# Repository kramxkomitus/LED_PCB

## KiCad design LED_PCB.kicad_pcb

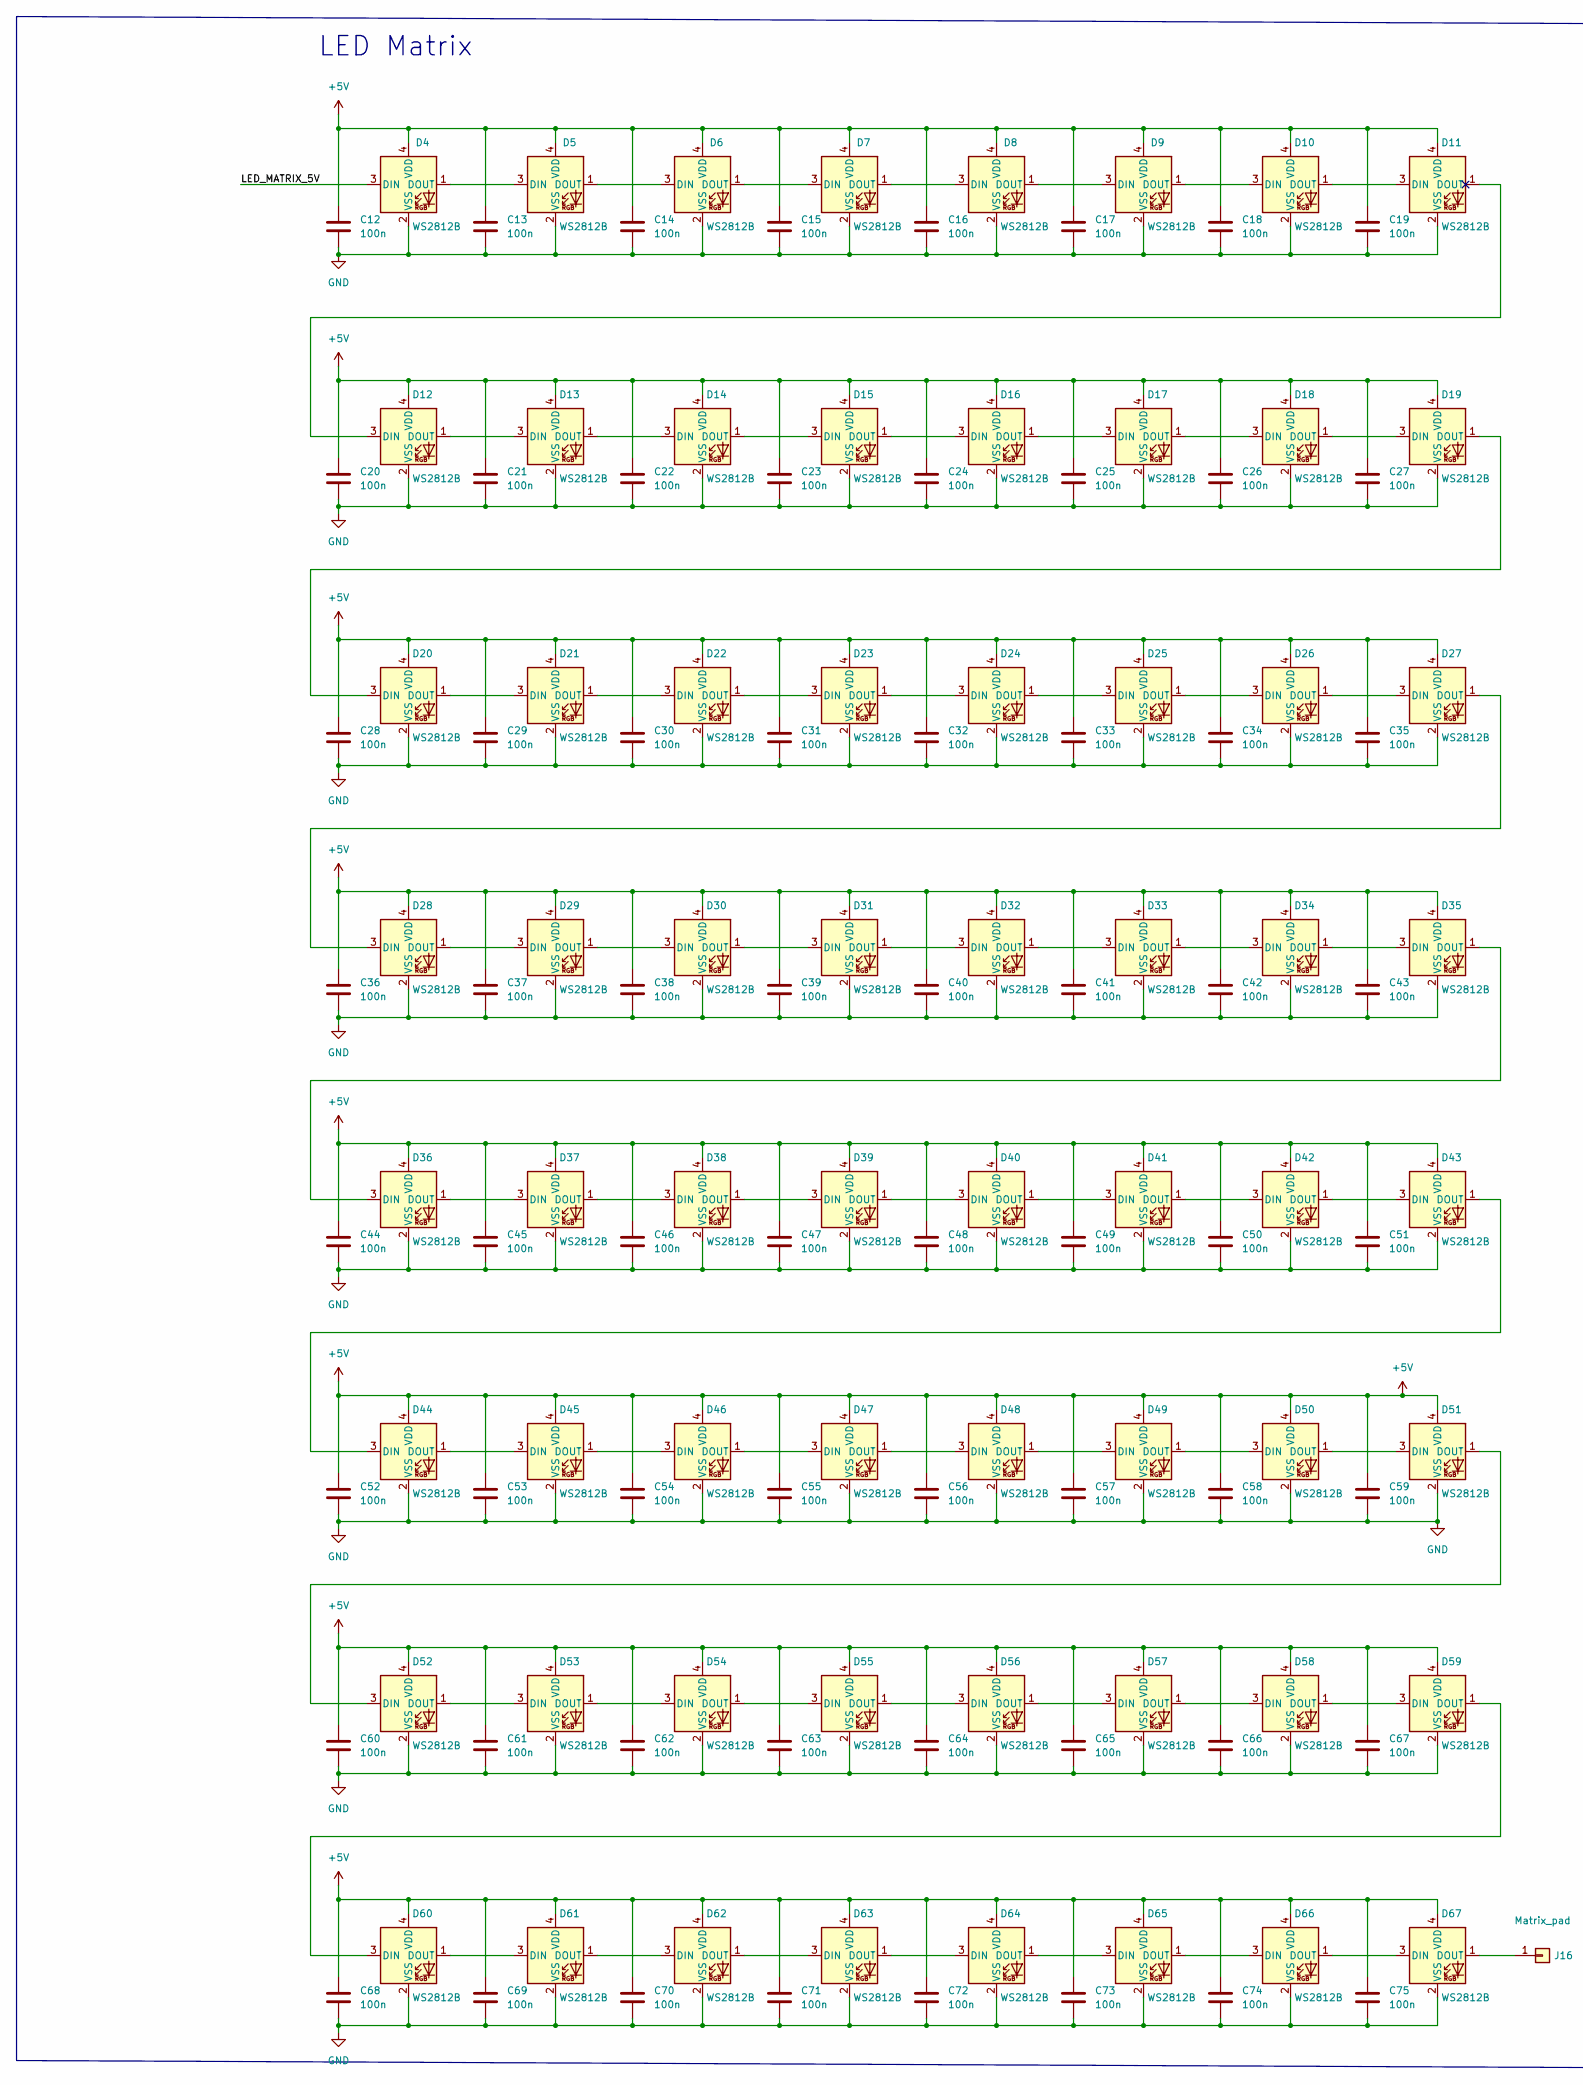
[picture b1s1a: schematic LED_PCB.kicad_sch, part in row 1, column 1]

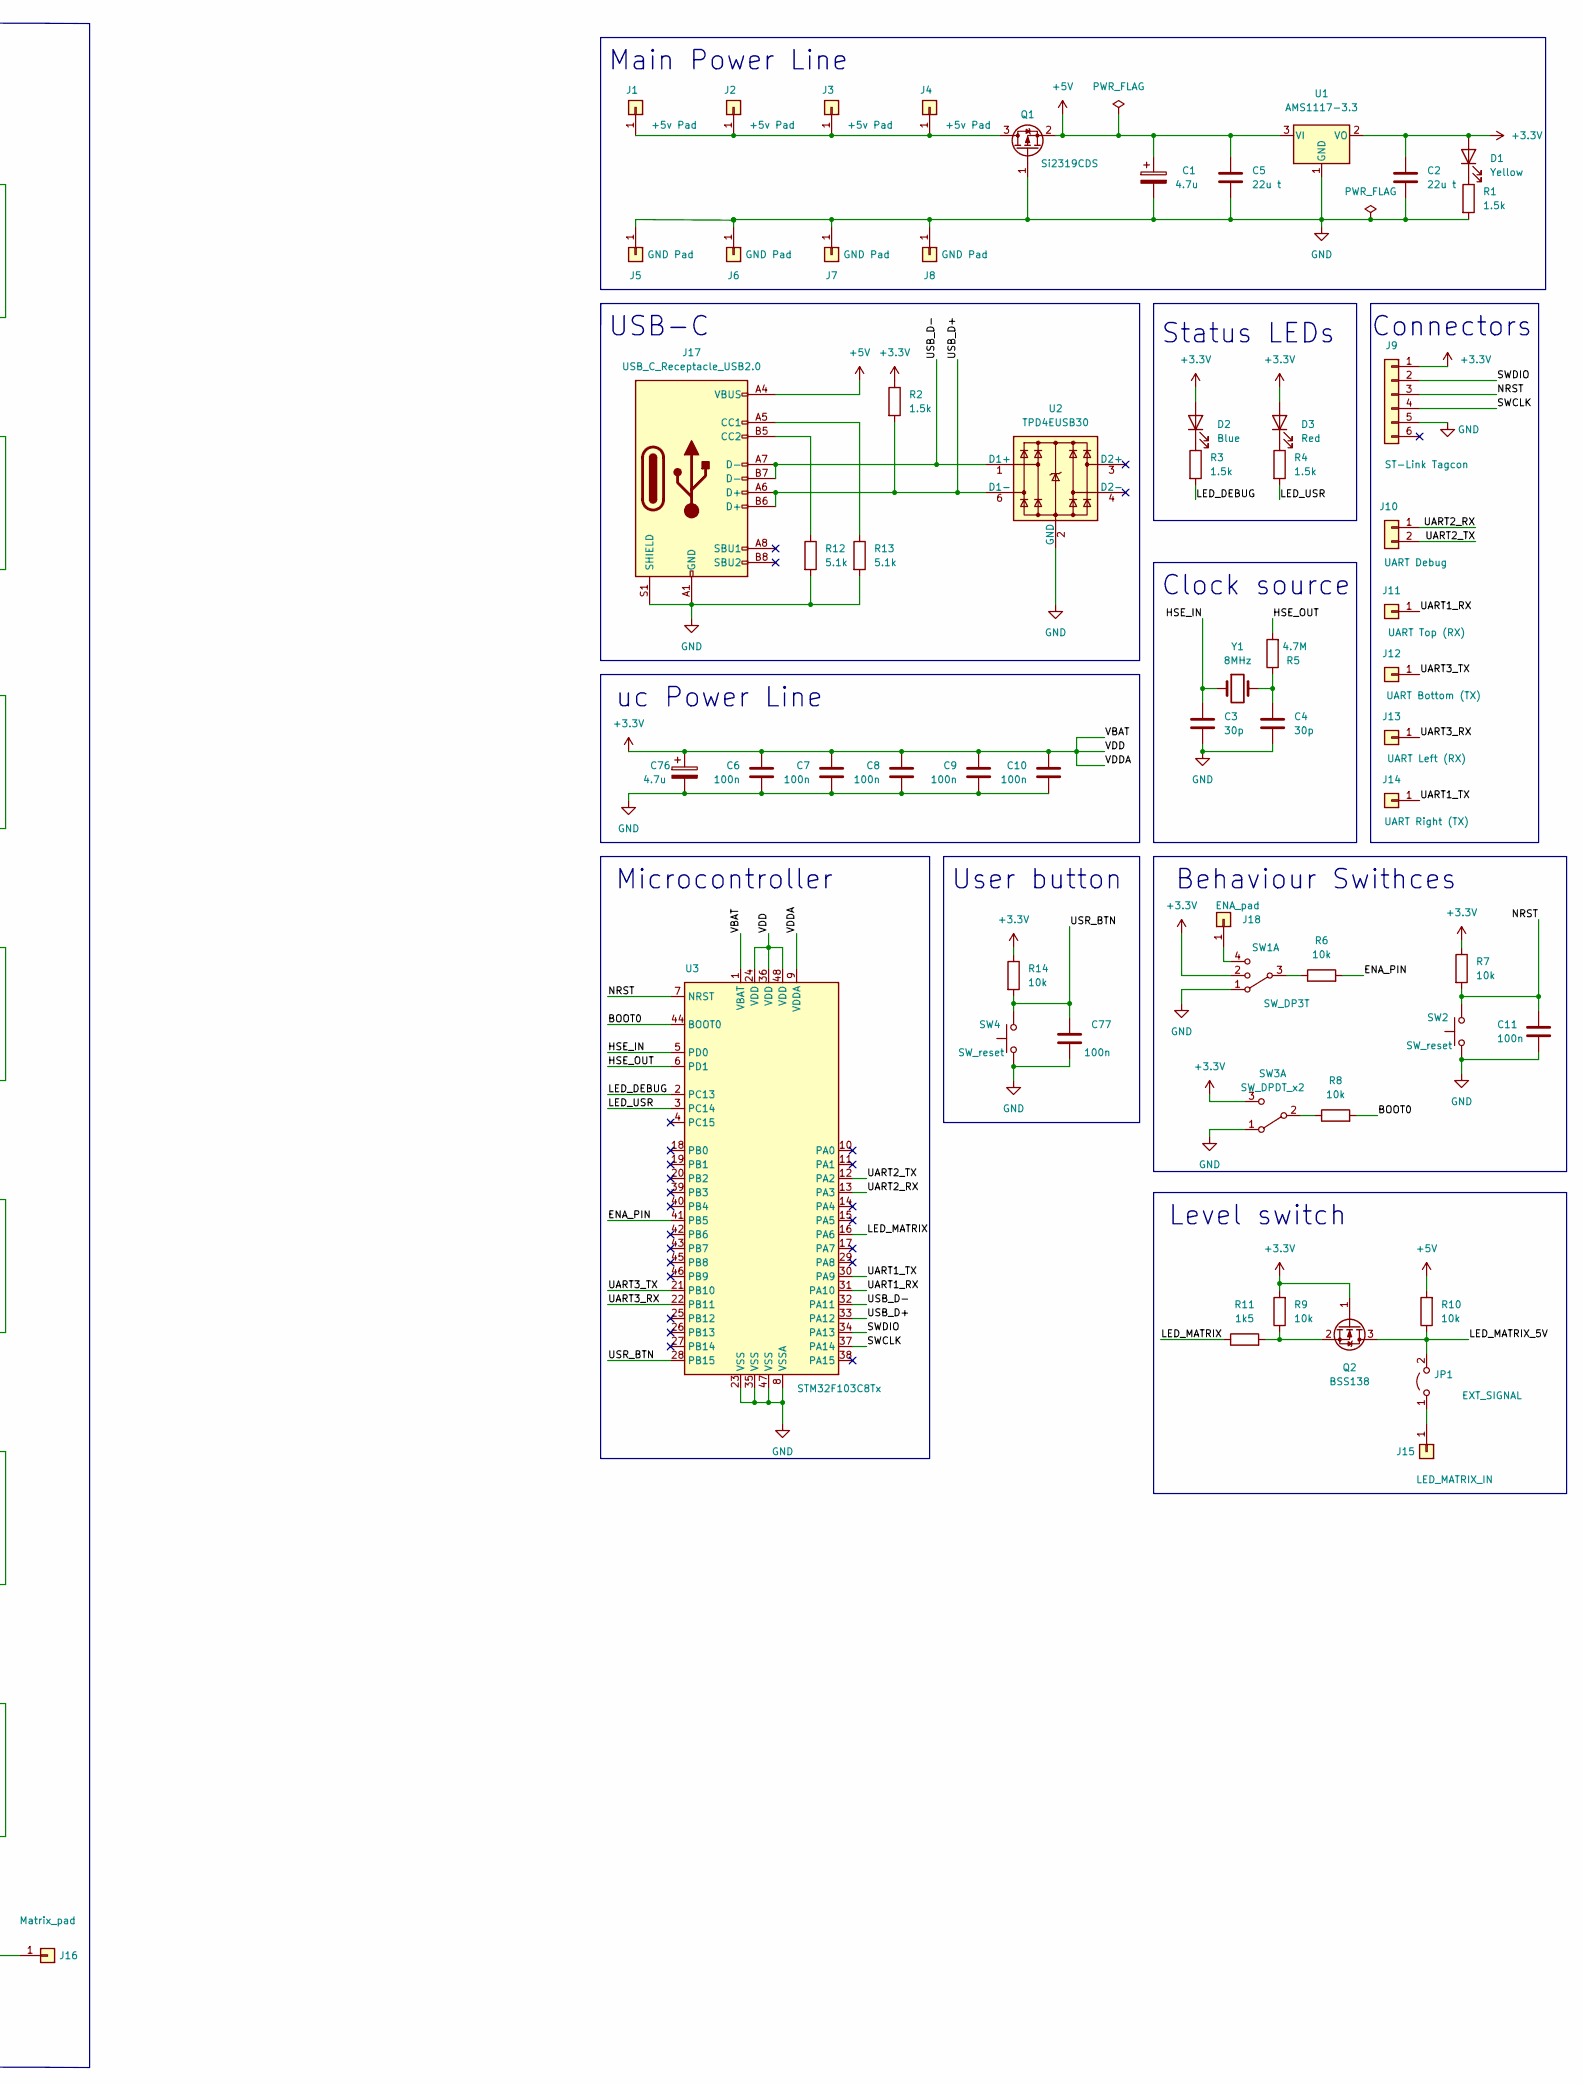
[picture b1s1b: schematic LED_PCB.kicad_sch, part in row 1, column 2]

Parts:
C1, C76: 4.7u; CP_EIA-3216-12_Kemet-S
C2, C5: 22u t; C_0805_2012Metric
C3, C4: 30p; C_0402_1005Metric
C6, C7, C8, C9, C10, C11, C12, C13, C14, C15, C16, C17, C18, C19, C20, C21, C22, C23, C24, C25, C26, C27, C28, C29, C30, C31, C32, C33, C34, C35, C36, C37, C38, C39, C40, C41, C42, C43, C44, C45, C46, C47, C48, C49, C50, C51, C52, C53, C54, C55, C56, C57, C58, C59, C60, C61, C62, C63, C64, C65, C66, C67, C68, C69, C70, C71, C72, C73, C74, C75, C77: 100n; C_0201_0603Metric
D1: Yellow; LED_0402_1005Metric
D2: Blue; LED_0402_1005Metric
D3: Red; LED_0402_1005Metric
D4, D5, D6, D7, D8, D9, D10, D11, D12, D13, D14, D15, D16, D17, D18, D19, D20, D21, D22, D23, D24, D25, D26, D27, D28, D29, D30, D31, D32, D33, D34, D35, D36, D37, D38, D39, D40, D41, D42, D43, D44, D45, D46, D47, D48, D49, D50, D51, D52, D53, D54, D55, D56, D57, D58, D59, D60, D61, D62, D63, D64, D65, D66, D67: WS2812B; LED-2020
J1, J2, J3, J4: +5v Pad; MountingHole_2.2mm_M2_DIN965_Pad_TopOnly
J5, J6, J7, J8: GND Pad; MountingHole_2.2mm_M2_DIN965_Pad_TopOnly
J9: ST-Link Tagcon; Tag-Connect_TC2030-IDC-NL_2x03_P1.27mm_Vertical
J10: UART Debug; TestPoint_2Pads_Pitch2.54mm_Drill0.8mm
J11: UART Top (RX); MountingHole_2.2mm_M2_DIN965_Pad_TopOnly
J12: UART Bottom (TX); MountingHole_2.2mm_M2_DIN965_Pad_TopOnly
J13: UART Left (RX); MountingHole_2.2mm_M2_DIN965_Pad_TopOnly
J14: UART Right (TX); MountingHole_2.2mm_M2_DIN965_Pad_TopOnly
J15: LED_MATRIX_IN; MountingHole_2.2mm_M2_DIN965_Pad_TopOnly
J16: Matrix_pad; MountingHole_2.2mm_M2_DIN965_Pad_TopOnly
J17: USB_C_Receptacle_USB2.0; USB_C_Connector_16P_SMD
J18: ENA_pad; TestPoint_Keystone_5000-5004_Miniature
JP1: EXT_SIGNAL; SolderJumper-2_P1.3mm_Open_TrianglePad1.0x1.5mm
Q1: Si2319CDS; SOT-23
Q2: BSS138; SOT-23
R1, R2, R3, R4: 1.5k; R_0402_1005Metric
R5: 4.7M; R_0402_1005Metric
R6, R7, R8, R9, R10, R14: 10k; R_0402_1005Metric
R11: 1k5; R_0402_1005Metric
R12, R13: 5.1k; R_0402_1005Metric
SW1: SW_DP3T; SW_SP3T_PCM13
SW2, SW4: SW_reset; SW_Push_1P1T_NO_Vertical_Wuerth_434133025816
SW3: SW_DPDT_x2; SW_SPDT_PCM12
U1: AMS1117-3.3; SOT-223-3_TabPin2
U2: TPD4EUSB30; SOT-23-6
U3: STM32F103C8Tx; LQFP-48_7x7mm_P0.5mm
Y1: 8MHz; Crystal_SMD_5032-2Pin_5.0x3.2mm

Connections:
+3V3: C2.1, C6.1, C7.1, C8.1, C9.1, C10.1, C76.1, D1.2 (A), D2.2 (A), D3.2 (A), J9.1, Q2.1 (G), R2.1, R7.1, R9.2, R14.1, SW1.2, SW3.3 (C), U1.2 (VO), U3.1 (VBAT), U3.9 (VDDA), U3.24 (VDD), U3.36 (VDD), U3.48 (VDD)
+5V: C1.1, C5.1, C12.1, C13.1, C14.1, C15.1, C16.1, C17.1, C18.1, C19.1, C20.1, C21.1, C22.1, C23.1, C24.1, C25.1, C26.1, C27.1, C28.1, C29.1, C30.1, C31.1, C32.1, C33.1, C34.1, C35.1, C36.1, C37.1, C38.1, C39.1, C40.1, C41.1, C42.1, C43.1, C44.1, C45.1, C46.1, C47.1, C48.1, C49.1, C50.1, C51.1, C52.1, C53.1, C54.1, C55.1, C56.1, C57.1, C58.1, C59.1, C60.1, C61.1, C62.1, C63.1, C64.1, C65.1, C66.1, C67.1, C68.1, C69.1, C70.1, C71.1, C72.1, C73.1, C74.1, C75.1, D4.4 (VDD), D5.4 (VDD), D6.4 (VDD), D7.4 (VDD), D8.4 (VDD), D9.4 (VDD), D10.4 (VDD), D11.4 (VDD), D12.4 (VDD), D13.4 (VDD), D14.4 (VDD), D15.4 (VDD), D16.4 (VDD), D17.4 (VDD), D18.4 (VDD), D19.4 (VDD), D20.4 (VDD), D21.4 (VDD), D22.4 (VDD), D23.4 (VDD), D24.4 (VDD), D25.4 (VDD), D26.4 (VDD), D27.4 (VDD), D28.4 (VDD), D29.4 (VDD), D30.4 (VDD), D31.4 (VDD), D32.4 (VDD), D33.4 (VDD), D34.4 (VDD), D35.4 (VDD), D36.4 (VDD), D37.4 (VDD), D38.4 (VDD), D39.4 (VDD), D40.4 (VDD), D41.4 (VDD), D42.4 (VDD), D43.4 (VDD), D44.4 (VDD), D45.4 (VDD), D46.4 (VDD), D47.4 (VDD), D48.4 (VDD), D49.4 (VDD), D50.4 (VDD), D51.4 (VDD), D52.4 (VDD), D53.4 (VDD), D54.4 (VDD), D55.4 (VDD), D56.4 (VDD), D57.4 (VDD), D58.4 (VDD), D59.4 (VDD), D60.4 (VDD), D61.4 (VDD), D62.4 (VDD), D63.4 (VDD), D64.4 (VDD), D65.4 (VDD), D66.4 (VDD), D67.4 (VDD), J17.A4 (VBUS), J17.A9 (VBUS), J17.B4 (VBUS), J17.B9 (VBUS), Q1.2 (S), R10.2, U1.3 (VI)
/BOOT0: R8.2, U3.44 (BOOT0)
/ENA_PIN: R6.2, U3.41 (PB5)
/HSE_IN: C3.1, U3.5 (PD0), Y1.1
/HSE_OUT: R5.2, U3.6 (PD1)
/LED_DEBUG: R3.2, U3.2 (PC13)
/LED_MATRIX: R11.1, U3.16 (PA6)
/LED_MATRIX_5V: D4.3 (DIN), JP1.2 (B), Q2.3 (D), R10.1
/LED_USR: R4.2, U3.3 (PC14)
/NRST: C11.1, J9.3, R7.2, SW2.2, U3.7 (NRST)
/SWCLK: J9.4, U3.37 (PA14)
/SWDIO: J9.2, U3.34 (PA13)
/UART1_RX: J11.1, U3.31 (PA10)
/UART1_TX: J14.1, U3.30 (PA9)
/UART2_RX: J10.1, U3.13 (PA3)
/UART2_TX: J10.2, U3.12 (PA2)
/UART3_RX: J13.1, U3.22 (PB11)
/UART3_TX: J12.1, U3.21 (PB10)
/USB_D+: J17.A6 (D+), J17.B6 (D+), R2.2, U2.6 (D1-), U3.33 (PA12)
/USB_D-: J17.A7 (D-), J17.B7 (D-), U2.1 (D1+), U3.32 (PA11)
/USR_BTN: C77.1, R14.2, SW4.2, U3.28 (PB15)
GND: C1.2, C2.2, C3.2, C4.2, C5.2, C6.2, C7.2, C8.2, C9.2, C10.2, C11.2, C12.2, C13.2, C14.2, C15.2, C16.2, C17.2, C18.2, C19.2, C20.2, C21.2, C22.2, C23.2, C24.2, C25.2, C26.2, C27.2, C28.2, C29.2, C30.2, C31.2, C32.2, C33.2, C34.2, C35.2, C36.2, C37.2, C38.2, C39.2, C40.2, C41.2, C42.2, C43.2, C44.2, C45.2, C46.2, C47.2, C48.2, C49.2, C50.2, C51.2, C52.2, C53.2, C54.2, C55.2, C56.2, C57.2, C58.2, C59.2, C60.2, C61.2, C62.2, C63.2, C64.2, C65.2, C66.2, C67.2, C68.2, C69.2, C70.2, C71.2, C72.2, C73.2, C74.2, C75.2, C76.2, C77.2, D4.2 (VSS), D5.2 (VSS), D6.2 (VSS), D7.2 (VSS), D8.2 (VSS), D9.2 (VSS), D10.2 (VSS), D11.2 (VSS), D12.2 (VSS), D13.2 (VSS), D14.2 (VSS), D15.2 (VSS), D16.2 (VSS), D17.2 (VSS), D18.2 (VSS), D19.2 (VSS), D20.2 (VSS), D21.2 (VSS), D22.2 (VSS), D23.2 (VSS), D24.2 (VSS), D25.2 (VSS), D26.2 (VSS), D27.2 (VSS), D28.2 (VSS), D29.2 (VSS), D30.2 (VSS), D31.2 (VSS), D32.2 (VSS), D33.2 (VSS), D34.2 (VSS), D35.2 (VSS), D36.2 (VSS), D37.2 (VSS), D38.2 (VSS), D39.2 (VSS), D40.2 (VSS), D41.2 (VSS), D42.2 (VSS), D43.2 (VSS), D44.2 (VSS), D45.2 (VSS), D46.2 (VSS), D47.2 (VSS), D48.2 (VSS), D49.2 (VSS), D50.2 (VSS), D51.2 (VSS), D52.2 (VSS), D53.2 (VSS), D54.2 (VSS), D55.2 (VSS), D56.2 (VSS), D57.2 (VSS), D58.2 (VSS), D59.2 (VSS), D60.2 (VSS), D61.2 (VSS), D62.2 (VSS), D63.2 (VSS), D64.2 (VSS), D65.2 (VSS), D66.2 (VSS), D67.2 (VSS), J5.1, J6.1, J7.1, J8.1, J9.5, J17.A1 (GND), J17.A12 (GND), J17.B1 (GND), J17.B12 (GND), J17.S1 (SHIELD), Q1.1 (G), R1.2, R12.2, R13.2, SW1.1, SW2.1, SW3.1 (A), SW4.1, U1.1 (GND), U2.2 (GND), U3.8 (VSSA), U3.23 (VSS), U3.35 (VSS), U3.47 (VSS)
unnamed: C4.1, R5.1, Y1.2
unnamed: D1.1 (K), R1.1
unnamed: D2.1 (K), R3.1
unnamed: D3.1 (K), R4.1
unnamed: D4.1 (DOUT), D5.3 (DIN)
unnamed: D5.1 (DOUT), D6.3 (DIN)
unnamed: D6.1 (DOUT), D7.3 (DIN)
unnamed: D7.1 (DOUT), D8.3 (DIN)
unnamed: D8.1 (DOUT), D9.3 (DIN)
unnamed: D10.1 (DOUT), D11.3 (DIN)
unnamed: D9.1 (DOUT), D10.3 (DIN)
unnamed: D11.1 (DOUT), D12.3 (DIN)
unnamed: D12.1 (DOUT), D13.3 (DIN)
unnamed: D13.1 (DOUT), D14.3 (DIN)
unnamed: D14.1 (DOUT), D15.3 (DIN)
unnamed: D15.1 (DOUT), D16.3 (DIN)
unnamed: D16.1 (DOUT), D17.3 (DIN)
unnamed: D17.1 (DOUT), D18.3 (DIN)
unnamed: D18.1 (DOUT), D19.3 (DIN)
unnamed: D19.1 (DOUT), D20.3 (DIN)
unnamed: D20.1 (DOUT), D21.3 (DIN)
unnamed: D21.1 (DOUT), D22.3 (DIN)
unnamed: D22.1 (DOUT), D23.3 (DIN)
unnamed: D23.1 (DOUT), D24.3 (DIN)
unnamed: D24.1 (DOUT), D25.3 (DIN)
unnamed: D25.1 (DOUT), D26.3 (DIN)
unnamed: D26.1 (DOUT), D27.3 (DIN)
unnamed: D27.1 (DOUT), D28.3 (DIN)
unnamed: D28.1 (DOUT), D29.3 (DIN)
unnamed: D29.1 (DOUT), D30.3 (DIN)
unnamed: D30.1 (DOUT), D31.3 (DIN)
unnamed: D31.1 (DOUT), D32.3 (DIN)
unnamed: D32.1 (DOUT), D33.3 (DIN)
unnamed: D33.1 (DOUT), D34.3 (DIN)
unnamed: D34.1 (DOUT), D35.3 (DIN)
unnamed: D35.1 (DOUT), D36.3 (DIN)
unnamed: D36.1 (DOUT), D37.3 (DIN)
unnamed: D37.1 (DOUT), D38.3 (DIN)
unnamed: D38.1 (DOUT), D39.3 (DIN)
unnamed: D39.1 (DOUT), D40.3 (DIN)
unnamed: D40.1 (DOUT), D41.3 (DIN)
unnamed: D41.1 (DOUT), D42.3 (DIN)
unnamed: D42.1 (DOUT), D43.3 (DIN)
unnamed: D43.1 (DOUT), D44.3 (DIN)
unnamed: D44.1 (DOUT), D45.3 (DIN)
unnamed: D45.1 (DOUT), D46.3 (DIN)
unnamed: D46.1 (DOUT), D47.3 (DIN)
unnamed: D47.1 (DOUT), D48.3 (DIN)
unnamed: D48.1 (DOUT), D49.3 (DIN)
unnamed: D49.1 (DOUT), D50.3 (DIN)
unnamed: D50.1 (DOUT), D51.3 (DIN)
unnamed: D51.1 (DOUT), D52.3 (DIN)
unnamed: D52.1 (DOUT), D53.3 (DIN)
unnamed: D53.1 (DOUT), D54.3 (DIN)
unnamed: D54.1 (DOUT), D55.3 (DIN)
unnamed: D55.1 (DOUT), D56.3 (DIN)
unnamed: D56.1 (DOUT), D57.3 (DIN)
unnamed: D57.1 (DOUT), D58.3 (DIN)
unnamed: D58.1 (DOUT), D59.3 (DIN)
unnamed: D59.1 (DOUT), D60.3 (DIN)
unnamed: D60.1 (DOUT), D61.3 (DIN)
unnamed: D61.1 (DOUT), D62.3 (DIN)
unnamed: D62.1 (DOUT), D63.3 (DIN)
unnamed: D63.1 (DOUT), D64.3 (DIN)
unnamed: D64.1 (DOUT), D65.3 (DIN)
unnamed: D65.1 (DOUT), D66.3 (DIN)
unnamed: D66.1 (DOUT), D67.3 (DIN)
unnamed: D67.1 (DOUT), J16.1
unnamed: J1.1, J2.1, J3.1, J4.1, Q1.3 (D)
unnamed: J15.1, JP1.1 (A)
unnamed: J17.A5 (CC1), R13.1
unnamed: J17.B5 (CC2), R12.1
unnamed: J18.1, SW1.4
unnamed: Q2.2 (S), R9.1, R11.2
unnamed: R6.1, SW1.3
unnamed: R8.1, SW3.2 (B)

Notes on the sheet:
Level switch
User button
uc Power Line
Status LEDs
Behaviour Swithces
USB-C
Main Power Line
Clock source
Connectors
LED Matrix
Microcontroller

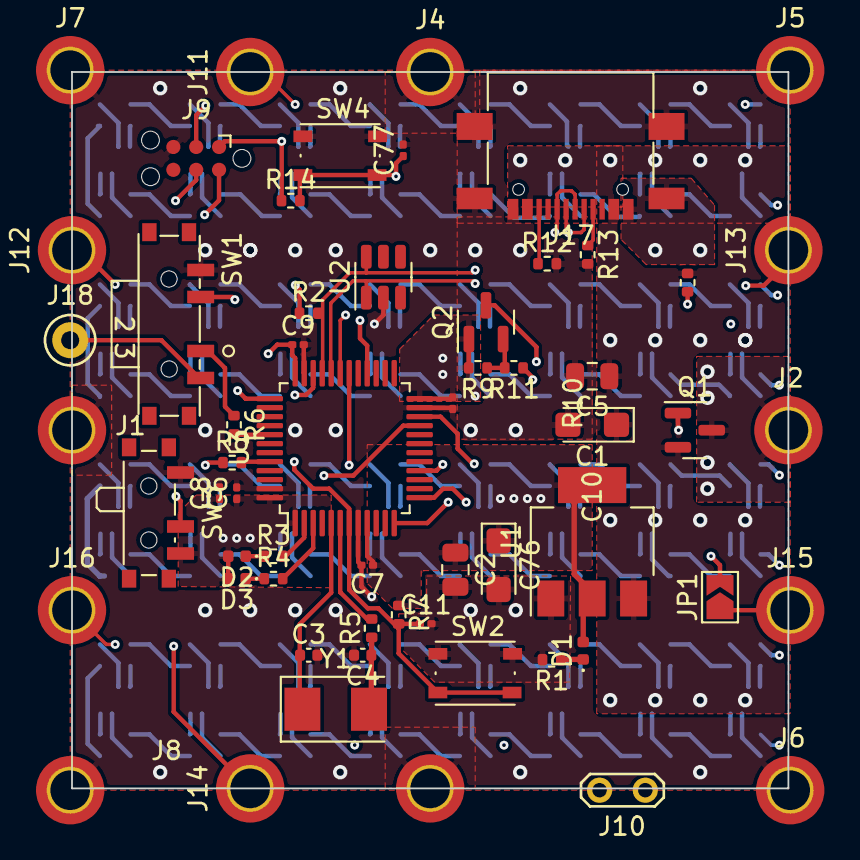
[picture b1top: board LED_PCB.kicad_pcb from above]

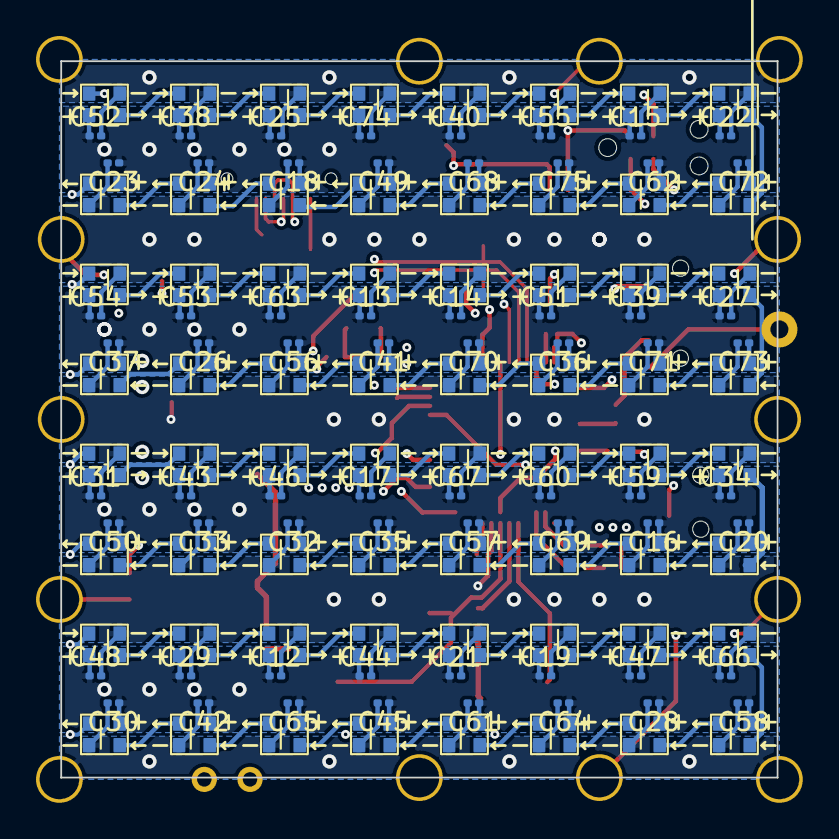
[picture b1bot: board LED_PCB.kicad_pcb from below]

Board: 4 copper layers, 39.8 x 39.8 mm, 187 parts (128 on the bottom side), 99 nets.

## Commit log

2024-09-01 Inited repo, added chematics
2024-09-23 Inited repo
2024-11-24 traced power polygons
2024-12-14 traced rawly
